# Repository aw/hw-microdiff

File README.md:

# μDiff: 10mbps over 1km on a single pair of wires

A simple 46mmx22.5mm module to route power and differential signals (RS-485) over RJ-45.

This project is also described in detail [on Hackaday.io](https://hackaday.io/project/179020-10mbps-over-1km-on-a-single-pair-of-wires)

It can be purchased as a kit **[from Tindie](https://www.tindie.com/products/24510/)**

This project is [certified open hardware](https://certification.oshwa.org/jp000009.html):

# How it works

μDiff provides an easy way to reliably transfer power and a digital signal over a long-distance using an inexpensive RJ-45 cable.

[](
https://www.youtube.com/watch?v=i-OBXi-Fx-U)

It uses RS-485 differential signaling and 802.3af Power-over-Ethernet pinouts to achieve this. It can accept an input voltage between 6.5V-12V, and provides outputs of 5V and 3.3V. All signals and voltages can be accessed through a 10-pin header. 

Current is limited to 1A. Beware of current limitations on the RJ-45 cable, it's typically ~350mA for an AWG26 shielded wire. 

# PCB features

  * Form factor 46mm x 22.5mm
  * Lead-free, RoHS compliant
  * Stackable with 4xM2 holes (1x grounded)
  * Open Source Hardware under [CC BY-SA 4.0](#License)
  * Easy to source off-the-shelf through-hole components
  * On-board (SMD 0603, 0805) capacitors, resistors, and diodes
  * Solder bridge jumpers to enable fail-safe biasing, termination, grounding.

### Top view

### Bottom view

See [images](images/) for more views.

# BOM (through-hole)

| Quantity | Item and Description | Datasheet |
| :----: | :---- | :---- |
| 1 | RJ45 Connector | [Assmann-RJ45-connector.pdf](datasheets/Assmann-RJ45-connector.pdf) |
| 1 | 10-pin (2x5) 2.54mm male of female header | |
| 1 | 3-pin (1x3) 2.54mm male or female header | |

# BOM (surface mount)

See [datasheets](datasheets/)

# Schematic

The schematic is available [here](schematic-v05.pdf)

# Notes

This PCB was designed with [Kicad](https://kicad.org/) v6.0 from the `debian buster-backports` repository.

I take no responsibility for any problems that may occur with your use of this PCB or design files. Create and use at your own risk.

# License

μDiff: 10mbps over 1km on a single pair of wires © 2021~ by [Alexander Williams](https://a1w.ca/) is licensed under [_CC BY-SA 4.0_ (Attribution-ShareAlike 4.0 International)](https://creativecommons.org/licenses/by-nc-sa/4.0/).

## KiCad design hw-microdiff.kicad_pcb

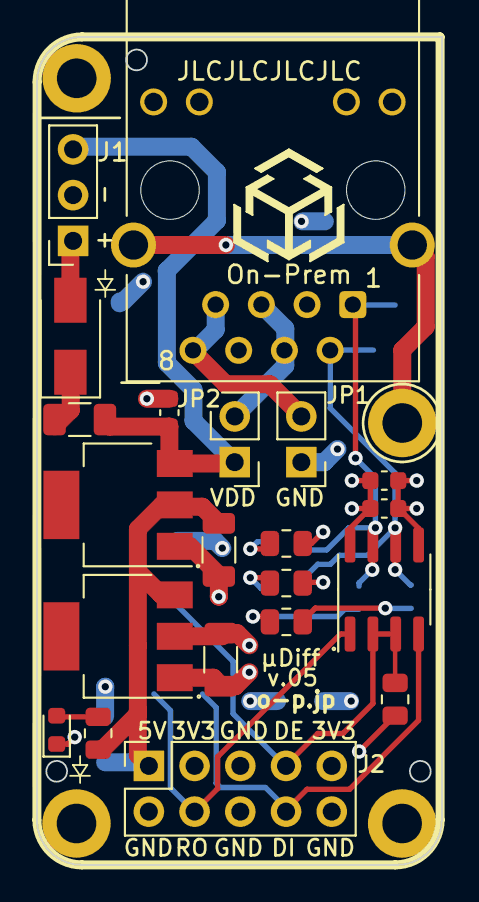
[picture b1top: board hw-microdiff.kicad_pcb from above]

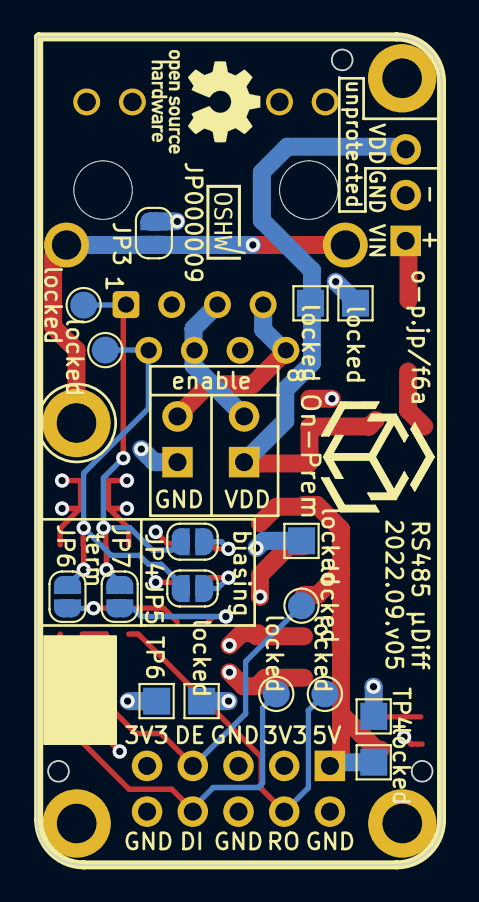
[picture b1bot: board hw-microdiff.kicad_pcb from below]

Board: 4 copper layers, 22.5 x 46.0 mm, 43 parts (18 on the bottom side), 19 nets.

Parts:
C1, C4: 0.1uF 50V; C_0603_1608Metric
C2, C3: 22uF 10V; C_1206_3216Metric
C5: 10uF 10V; C_0603_1608Metric
D1: Diode 40V/3A; D_SMA
D2: Blue LED; LED_0603_1608Metric
F1: Fuse 24V/1A; Fuse_1206_3216Metric
H1, H2, H3, H4: M2_MountingHole; MountingHole_2.2mm_M2_ISO14580_Pad
J1: Power Input; PinSocket_1x03_P2.54mm_Vertical
J2: Header 2x5P; PinSocket_2x05_P2.54mm_Vertical
J3: 8P8C; RJ45_Hanrun_HR911105A
JP1: GND EN; PinHeader_1x02_P2.54mm_Vertical
JP2: VIN EN; PinHeader_1x02_P2.54mm_Vertical
JP3: Grounding; SolderJumper-2_P1.3mm_Open_RoundedPad1.0x1.5mm
JP4: Biasing-; SolderJumper-2_P1.3mm_Open_RoundedPad1.0x1.5mm
JP5: Biasing+; SolderJumper-2_P1.3mm_Open_RoundedPad1.0x1.5mm
JP6, JP7: Terminating; SolderJumper-2_P1.3mm_Open_RoundedPad1.0x1.5mm
OSHW_Mono_0.1_Scale: JP000009; OSHW_Mono_0.1_Scale
R1: 220R; R_0805_2012Metric
R2: 10K; R_0805_2012Metric
R3, R4: 390R; R_0805_2012Metric
R5: 100R; R_0805_2012Metric
TP4, TP6: TP_GND; TestPoint_Pad_1.5x1.5mm
U1: 5V/1A; SOT-223
U2: 3.3V/1A; SOT-223
U3: RS-485; SOIC-8_3.9x4.9mm_P1.27mm
locked: TP_VDD; TestPoint_Pad_1.5x1.5mm
locked#2, locked#8: TP_GND; TestPoint_Pad_1.5x1.5mm
locked#3: TP_5V; TestPoint_Pad_1.5x1.5mm
locked#4: TP_3V3; TestPoint_Pad_1.5x1.5mm
locked#5: TP_RO; TestPoint_Pad_D1.5mm
locked#6: TP_DI; TestPoint_Pad_D1.5mm
locked#7: TP_DE_RE; TestPoint_Pad_D1.5mm
locked#9: TP_A1; TestPoint_Pad_D1.5mm
locked#10: TP_B1; TestPoint_Pad_D1.5mm

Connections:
+3V3: C3.2, C4.1, C5.1, J2.3, J2.9, R3.2, U2.2 (VO), U3.8 (VCC), locked#4.1
+5V: C2.1, J2.1, R1.1, U1.2 (VO), U2.3 (VI), locked#3.1
/A1+: JP5.2 (B), R3.1
/A1-: JP4.2 (B), R4.1
/A2+: JP6.2 (B), R5.1
/A2-: JP7.2 (B), R5.2
/A+: J3.2, JP5.1 (A), JP6.1 (A), U3.6 (A), locked#9.1
/A-: J3.1, JP4.1 (A), JP7.1 (A), U3.7 (B), locked#10.1
/DE_RE: J2.7, R2.1, U3.2 (~RE), U3.3 (DE), locked#7.1
/DI: J2.8, U3.4 (DI), locked#6.1
/RO: J2.4, U3.1 (RO), locked#5.1
/VDD: C1.1, F1.2, J1.3, JP2.1 (A), U1.3 (VI), locked.1
/VIN: D1.2 (A), J1.1
Earth: H2.1, J3.SH, JP3.1 (A)
GND: C1.2, C2.2, C3.1, C4.2, C5.2, D2.1 (K), J1.2, J2.2, J2.5, J2.6, J2.10, JP1.1 (A), JP3.2 (B), R2.2, R4.2, TP4.1, TP6.1, U1.1 (GND), U2.1 (GND), U3.5 (GND), locked#2.1, locked#8.1
unnamed: D1.1 (K), F1.1
unnamed: D2.2 (A), R1.2
unnamed: J3.4, J3.5, JP2.2 (B)
unnamed: J3.7, J3.8, JP1.2 (B)

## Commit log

2021-08-05 Add README and schematic
2021-08-05 Add link to video demo
2021-08-10 Add design files and update license
2021-08-12 Add certified OSHWA open hardware logo
2021-08-12 Add BOM for through-hole components
2021-08-12 Upload the actual datasheets
2022-08-12 Finish PCB routing for v.04
2023-01-24 Minor layout corrections: - Add test pads on back of PCB - Remove 10K pullup - Adjust silkscreens - Update to KiCad 6.0 - Add 3D model for RJ45 connector - Add VDD pin for unprotected VIN - Add open 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
